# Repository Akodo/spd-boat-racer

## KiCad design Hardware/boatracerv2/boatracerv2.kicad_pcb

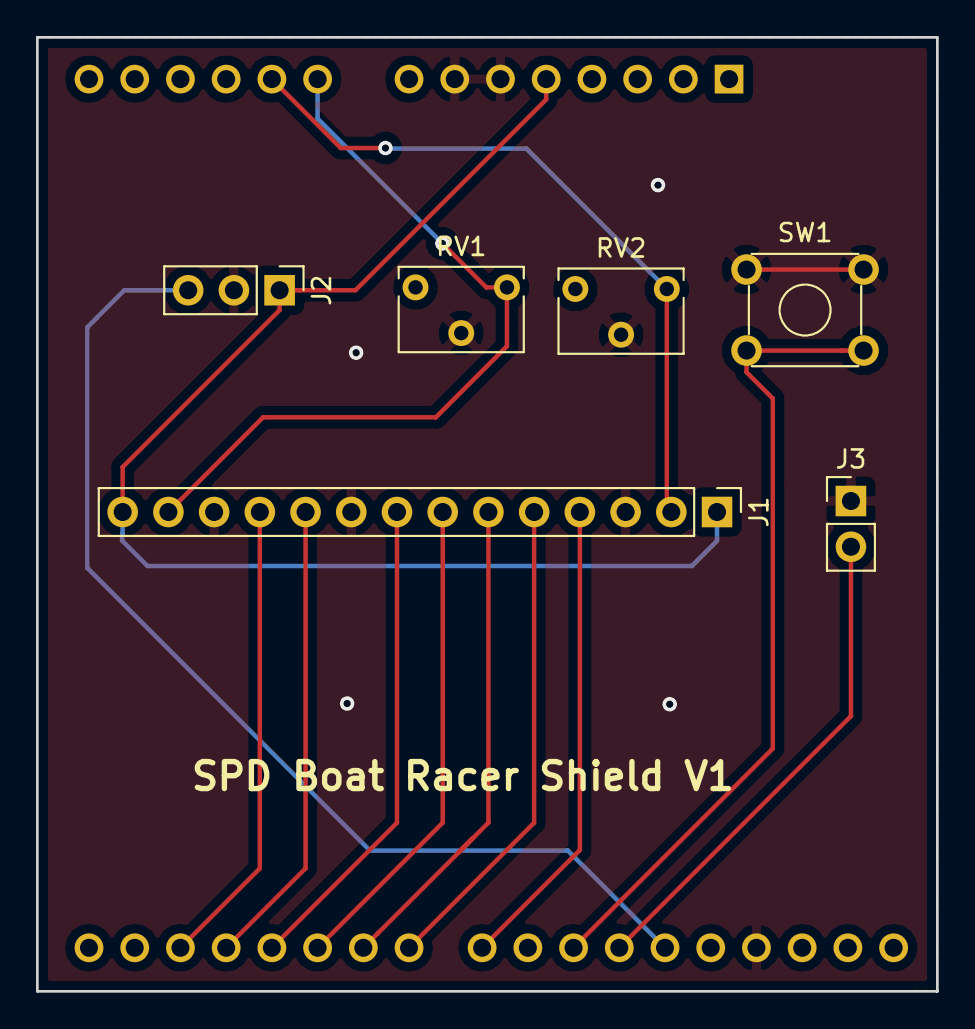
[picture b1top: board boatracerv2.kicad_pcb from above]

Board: 2 copper layers, 50.0 x 53.0 mm, 7 parts (1 on the bottom side), 14 nets.

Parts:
A1: Arduino_UNO_R3
J1: Screw_Terminal_01x14; PinHeader_1x14_P2.54mm_Vertical
J2: Conn_01x03_Male; PinHeader_1x03_P2.54mm_Vertical
J3: Screw_Terminal_01x02; PinHeader_1x02_P2.54mm_Vertical
RV1, RV2: 500K; Potentiometer_Bourns_3266W_Vertical
SW1: SW_Push; SW_TH_Tactile_Omron_B3F-10xx

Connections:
+5V: A1.5, J1.1, J1.14, J2.1
GND: A1.6, A1.7, A1.29, J1.3, J1.9, J1.12, J2.2, J3.1, RV1.2, RV2.2, SW1.2
unnamed: A1.9, J1.13, RV1.1
unnamed: A1.10, J1.2, RV2.1
unnamed: A1.17, J1.11
unnamed: A1.18, J1.10
unnamed: A1.19, J1.8
unnamed: A1.20, J1.7
unnamed: A1.21, J1.6
unnamed: A1.22, J1.5
unnamed: A1.23, J1.4
unnamed: A1.25, SW1.1
unnamed: A1.26, J3.2
unnamed: A1.27, J2.3

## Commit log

2019-02-03 intial commit
2019-02-08 Add CAD to hardware folder
2019-02-09 Improved false start logic
